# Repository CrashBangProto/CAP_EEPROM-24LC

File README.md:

#Toadstool-EEPROM-24LC

**Toadstool Cap - 24LC128 EEPROM Module**

The Toadstool family is made up of breadboard-friendly prototyping boards that house a microcontroller, and modules called *Caps* that connect using a standard header.  The prototyping board is analagous to an Arduino/Launchpad and the Cap analagous to a shield/boosterpack.

This repository contains the schematics for the **Toadstool-EEPROM-24LC Cap**, a 128kb EEPROM module that connects to  Toadstool prototyping boards using the common header.  The Microchip 24LC128 chip does all the work.

The boards were layed out using [KiCad](http://www.kicad-pcb.org) - KiCad is open source and awesome.

There are a number of other CrashBangProto respositories containing the schematics for other Toadstool boards and Caps, as well as sample code to get you up and running.

Visit the [Toadstool Webpages](http://www.crash-bang.com/projects/toadstool/) for more information on the project.

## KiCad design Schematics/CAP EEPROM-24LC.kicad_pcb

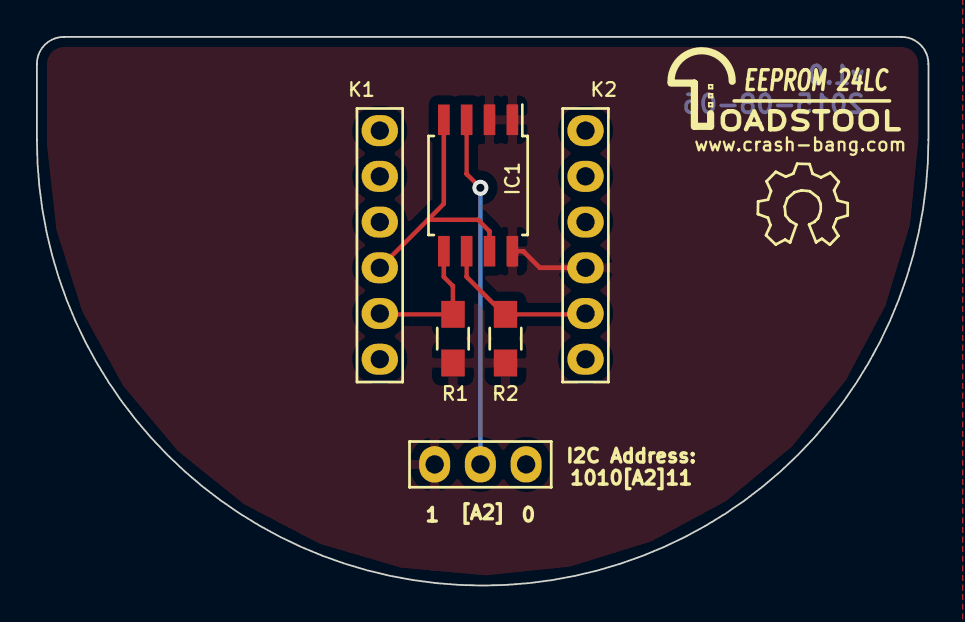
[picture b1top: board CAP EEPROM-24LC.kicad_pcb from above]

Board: 2 copper layers, 49.5 x 30.5 mm, 7 parts (0 on the bottom side), 5 nets.

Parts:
IC1: 24LC128; SOIJ-8_5.3x5.3mm_Pitch1.27mm
K1: CAP_CONN_LHS; Socket_Strip_Stackable_1x06
K2: CAP_CONN_RHS; Socket_Strip_Stackable_1x06
P1: A2_SEL; Pin_Header_Straight_1x03
R1, R2: 10k; R_0805_HandSoldering
Toadstool_Logo: LOGO**; Toadstool_Logo

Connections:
/SCL: IC1.6, K2.5, R2.2
/SDA: IC1.5, K1.5, R1.2
GND: IC1.4, IC1.7, K1.4, P1.1
unnamed: IC1.3, P1.2
VCC: IC1.1, IC1.2, IC1.8, K2.4, P1.3, R1.1, R2.1

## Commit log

2015-05-15 :neckbeard: Added .gitattributes
2015-08-19 Cosmetic Changes to Silkscreen
    Cosmetic Changes to Silkscreen
